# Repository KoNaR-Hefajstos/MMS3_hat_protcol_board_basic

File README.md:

# Zestaw template'ów kompatybilnych z płytką MMS3 i systemem ChainBus

### Łączenie hat'ów
<p> Na jednym MMS3 można zamontować do 8 hatów. Łączy się przez wpinianie kolejnego Hat'a do złącza ChainBus wcześniejszego

### Komunikacja oraz sterowanie
<p> ChainBus jest w pełni cyfrowy. GPIO nie sterują bezpośrednio funkcjonalnością, tylko poprzez magistrale komunikacyjne i IC.
<p> Znaczy to, że zamiast używać GPIO do przełączania LED'a, odczytywania krańcówek czy zadawania PWM'a musisz zaimplementować jakiegoś IC który to robi. Np:
<p> MCU --> expander gpio po I2C --> Dioda LED
<p> MCU wybiera do którego hat'a się podpina przy użyciu bus switcha. To znaczy że magistrale I2C, SPI i UART są niezależne od siebie na każdym hat'ie (nie musisz się martwić o zajęte adresy I2C). Ale musisz pamiętać żeby podpinać sie z busa Chainbus a nie Chainbus_IN (czyli tego za bus swichem)
<p> Dodatkowo w celu identyfikacji każdego hat'a jest na nim pamięć EEPROM po I2C. Możesz użyć np. M24C64-W z obudową SOIC-8 i addresie 1010000 (przy A0 A1 A2 zwartych do GND)

### Zasilanie
<p> Przez złącze ChainBus idzie następujące zasilanie

|          |   Napięcie    | Prąd na wszystkie haty | Prąd dla jednego hat'a |
| -------- | :-----------: | :--------------------: | ---------------------: |
| 5V       |      5V       |           1A           |                  125mA |
| 12V stby |      12V      |          0.5A          |                   65mA |
| BRD_VIN  | Od 12V do 48V |          1.5A          |                  185mA |

<p> Prąd dla jednego hat'a został policzony w wypadku kiedy wszystkie 8 hat'ów jest zamontowanych. Jeśli na jeden MMS zamontujesz mniej hat'ów to każdy może pociągnąć więcej prądu.

<p> Hat'y powinny obsługiwać do 48V z BRD_VIN. Komponenty powinny być dostosowane aż do tego napięcia.

<p> Jeśli twoja płytka potrzebuje więcej mocy niż ile ChainBus daje, to można dodatkowo podłączyć Vin po XT60 która obsługuje około 60A.

<p> Jeśli potrzebujesz innych napięć to możesz użyć gotowej przetwonicy step-down z template'a. Można wybierać z niej 24V, 12V, 9V i 6V2. Wszystkie na 2A.

### Template Mechaniczny
<p> Nie możesz zmieniać wielkości PCB, rozstawienia otworów montażowych oraz pozycji złącz chainbus (02x16 SMD, 2.54 raster) żeby płytka była kompatybilna z ChainBus'em
<p> Jeśli są potrzebne będą w twoim projekcie, to na płytce zostały rozstawione złącza XT60 oraz konwerter step down. Te elementy nie zostały jeszcze przetestowane, ale powinny działać.
<p>Jeśli twój projekt ich nie potrzebuje to możesz je na spokojnie usunąć.

### Wyprowadzenia
<p> Po środku płytki na górze jest złącze Chainbus. Na od front'u  jest żeńskie, na Back'u jest męskie.
<p> Na dolnej krawędzi płytki powinny być umieszczone złącza wyjścia/wejścia. Na lewej złacza XT60 jeśli ich używasz, a na prawej wszystkie elementy konfiguracyjne i debugowe (potencjometry, przyciski, LED'y).

<p> Domyślnie jako złącz używamy JST-XH 2.5mm. Producent mówi że obsługują do 3A

### Przykładowy hat
[Sterownik silników krokowych. Komunikacja po SPI](https://github.com/KoNaR-Hefajstos/MMS3_hat_stepper_controler)

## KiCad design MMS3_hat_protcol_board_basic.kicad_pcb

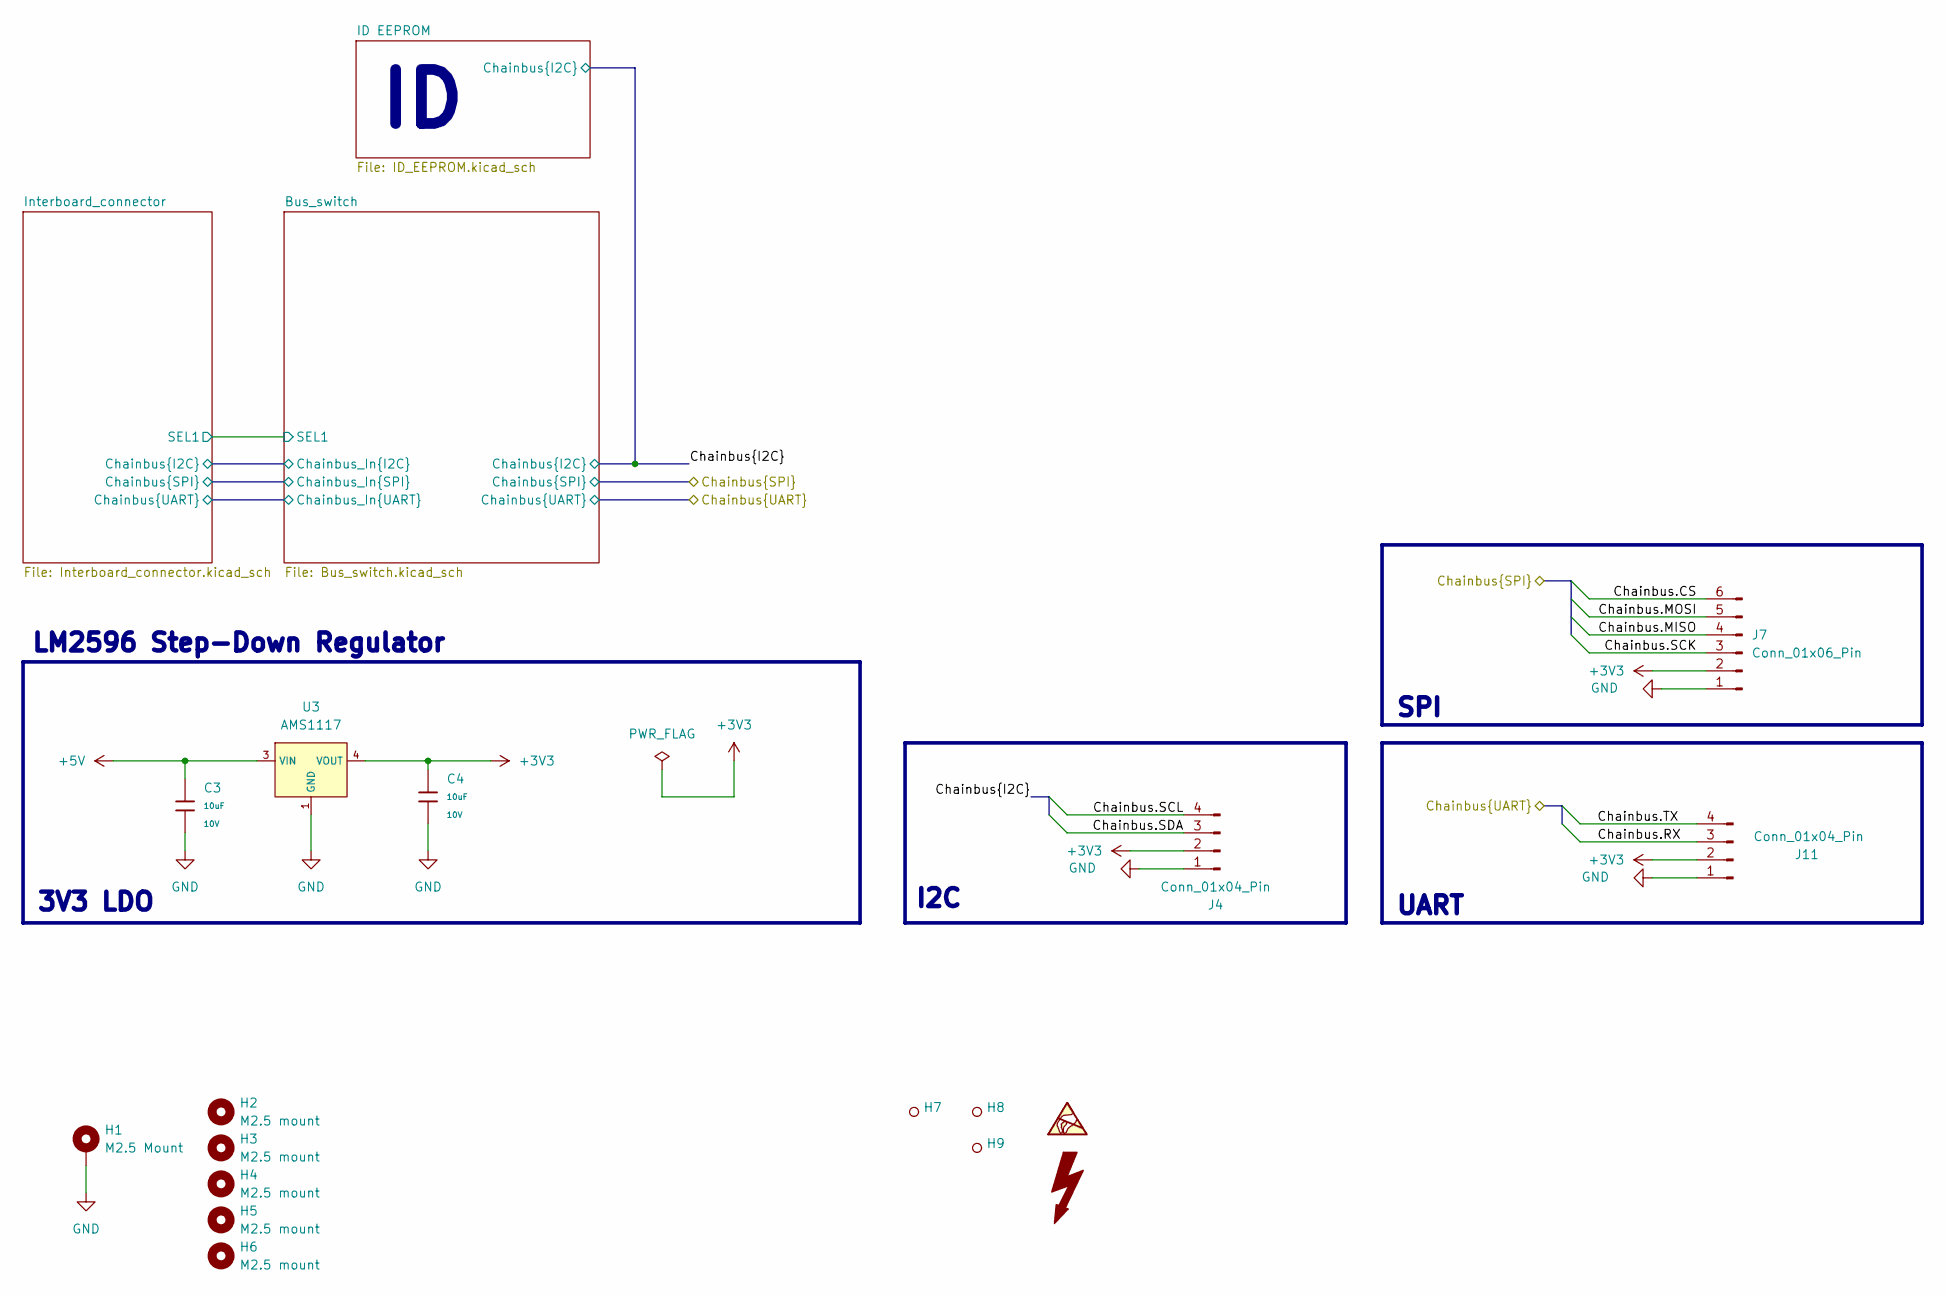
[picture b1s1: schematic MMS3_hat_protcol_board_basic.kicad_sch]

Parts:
C3, C4: 10uF; C_0603; Voltage Rated 10V; Tolerance ±10%; Part CL10A106KP8NNNC; LCSC C19702
H1: M2.5 Mount; MountingHole_2.7mm_M2.5_DIN965_Pad_TopOnly
H2, H3, H4, H5, H6: M2.5 mount; MountingHole_2.7mm_M2.5
H7, H8, H9: Hole_Tooling_JLCPCB
J4, J11: Conn_01x04_Pin; JST_XH_S4B-XH-A_1x04_P2.50mm_Horizontal
J7: Conn_01x06_Pin; JST_XH_S6B-XH-A_1x06_P2.50mm_Horizontal
U3: AMS1117; SOT-223-3_L6.5-W3.4-P2.30-LS7.0-BR; Output Voltage 3.3V; Dropout Voltage 1.3V@(800mA); Part AMS1117-3.3; LCSC C6186

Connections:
+3V3: C4.1, J4.2, J7.2, J11.2, U3.2 (VOUT), U3.4 (VOUT); also elsewhere on the board
+5V: C3.1, U3.3 (VIN); also elsewhere on the board
/Chainbus.CS: J7.6; also elsewhere on the board
/Chainbus.MISO: J7.4; also elsewhere on the board
/Chainbus.MOSI: J7.5; also elsewhere on the board
/Chainbus.RX: J11.3; also elsewhere on the board
/Chainbus.SCK: J7.3; also elsewhere on the board
/Chainbus.SCL: J4.4; also elsewhere on the board
/Chainbus.SDA: J4.3; also elsewhere on the board
/Chainbus.TX: J11.4; also elsewhere on the board
GND: C3.2, C4.2, H1.1 (1_1), J4.1, J7.1, J11.1, U3.1 (GND); also elsewhere on the board

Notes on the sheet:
3V3 LDO
SPI
I2C
LM2596 Step-Down Regulator
UART

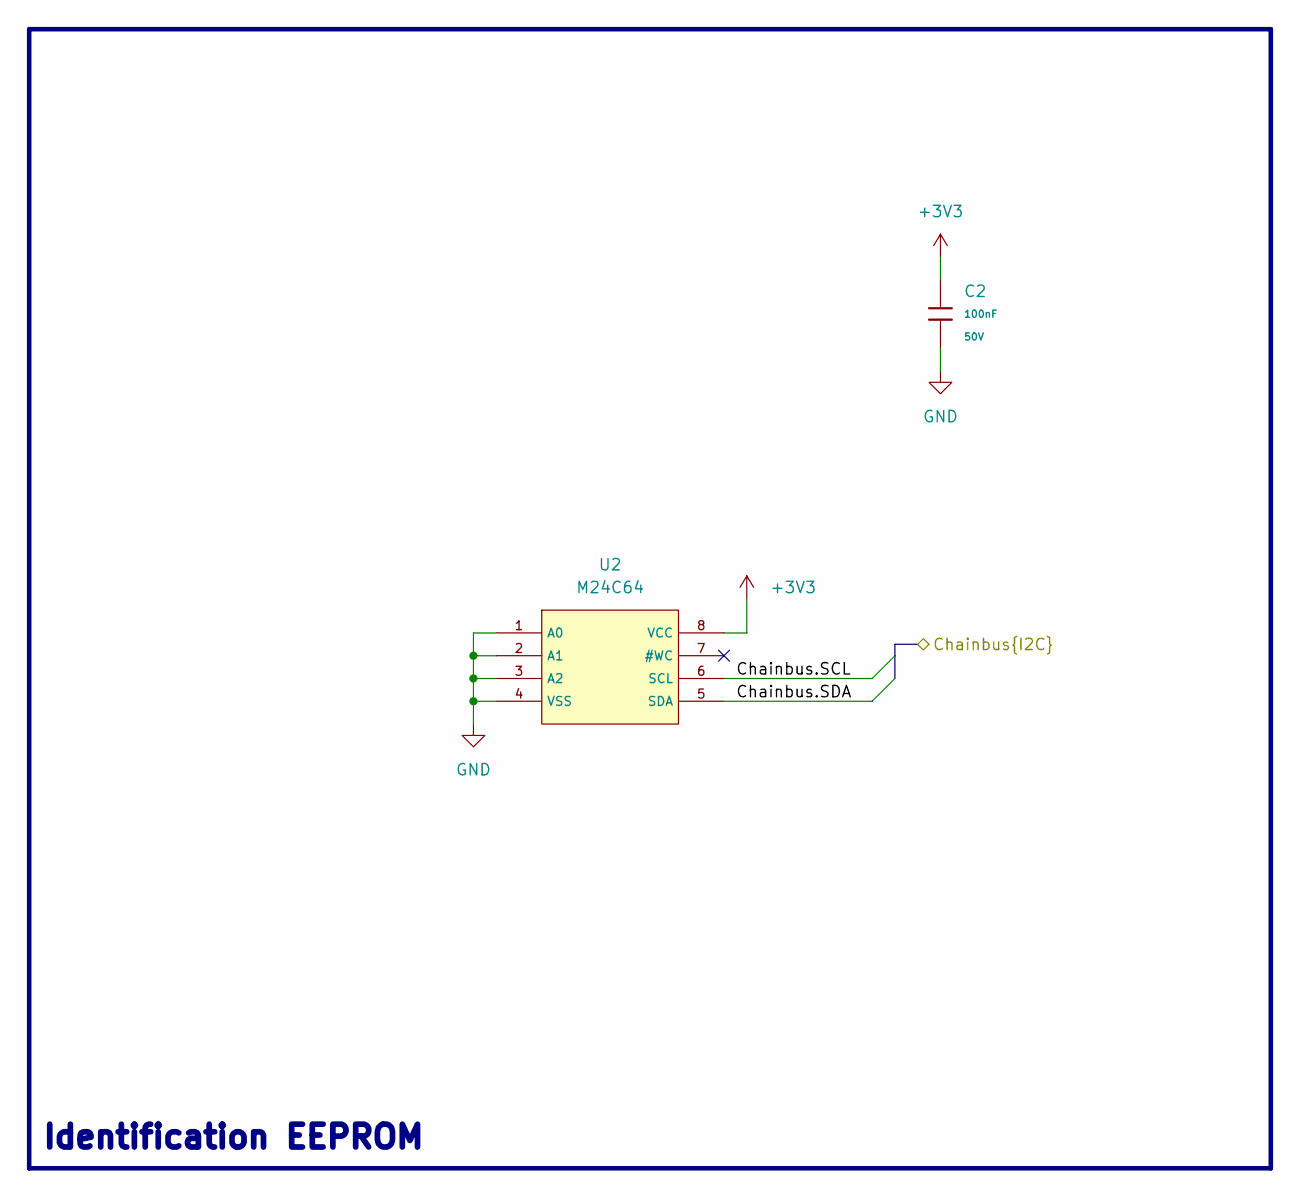
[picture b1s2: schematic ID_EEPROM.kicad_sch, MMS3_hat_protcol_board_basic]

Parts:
C2: 100nF; C_0603; Voltage Rated 50V; Tolerance ±10%; Part CC0603KRX7R9BB104; LCSC C14663
U2: M24C64; SOIC-8_L5.0-W4.0-P1.27-LS6.0-BL; Supply Voltage 1.8V~5.5V; Part M24C64-RMN6TP; LCSC C79988

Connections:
+3V3: C2.1, U2.8 (VCC); also elsewhere on the board
/Chainbus.SCL: U2.6 (SCL); also elsewhere on the board
/Chainbus.SDA: U2.5 (SDA); also elsewhere on the board
GND: C2.2, U2.1 (A0), U2.2 (A1), U2.3 (A2), U2.4 (VSS); also elsewhere on the board

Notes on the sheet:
Identification EEPROM

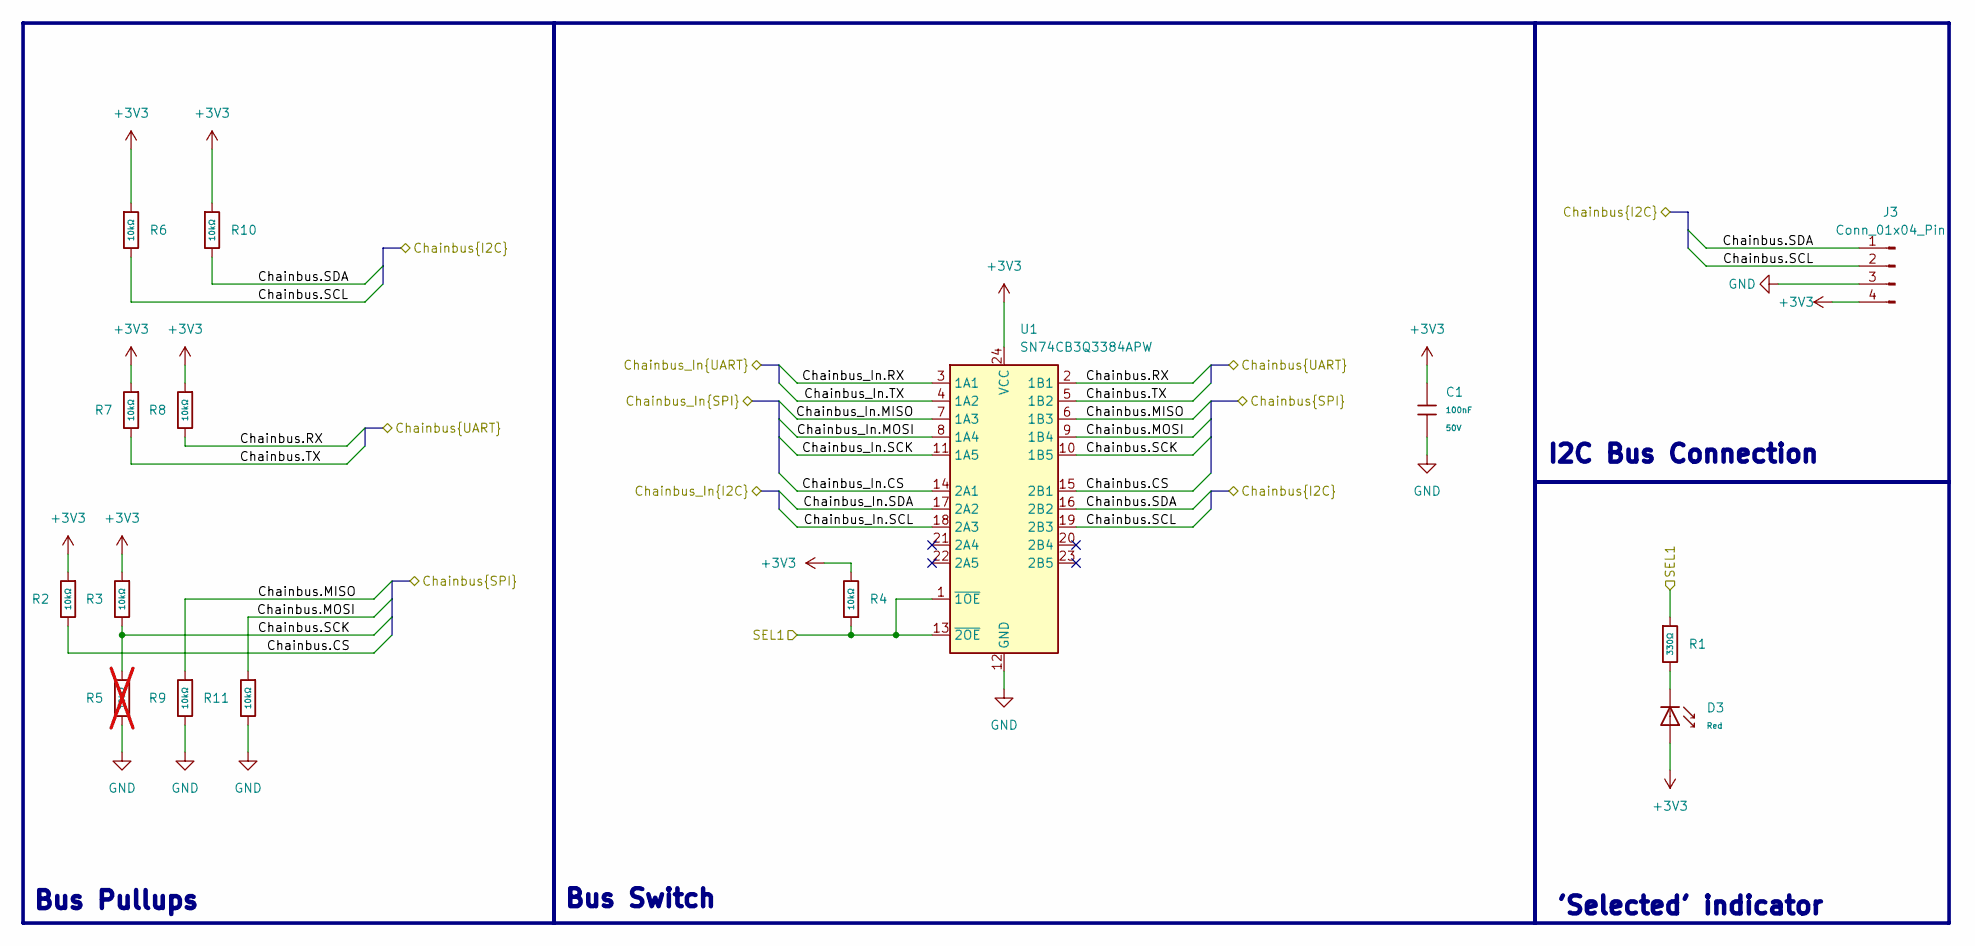
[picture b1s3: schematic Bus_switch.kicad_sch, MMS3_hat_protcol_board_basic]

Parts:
C1: 100nF; C_0603; Voltage Rated 50V; Tolerance ±10%; Part CC0603KRX7R9BB104; LCSC C14663
D3: Red; D_0603; Part KT-0603R; LCSC C2286
J3: Conn_01x04_Pin; PinHeader_1x04_P2.54mm_Vertical
R1: 330Ω; R_0402; Overload Voltage (Max) 50V; Tolerance ±1%; Part 0402WGF3300TCE; LCSC C25104
R2, R3, R4, R6, R7, R8, R9, R10, R11: 10kΩ; R_0402; Overload Voltage (Max) 50V; Tolerance ±1%; Part 0402WGF1002TCE; LCSC C25744
R5: 10kΩ; R_0402; Overload Voltage (Max) 50V; Tolerance ±1%; Part 0402WGF1002TCE; LCSC C25744; not fitted
U1: SN74CB3Q3384APW; TSSOP-24_4.4x7.8mm_P0.65mm; LCSC C469874

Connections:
+3V3: C1.1, D3.2, J3.4, R2.1, R3.1, R4.2, R6.1, R7.1, R8.1, R10.1, U1.24 (VCC); also elsewhere on the board
/Bus_switch/Chainbus_In.CS: U1.14 (2A1); also elsewhere on the board
/Bus_switch/Chainbus_In.MISO: U1.7 (1A3); also elsewhere on the board
/Bus_switch/Chainbus_In.MOSI: U1.8 (1A4); also elsewhere on the board
/Bus_switch/Chainbus_In.RX: U1.3 (1A1); also elsewhere on the board
/Bus_switch/Chainbus_In.SCK: U1.11 (1A5); also elsewhere on the board
/Bus_switch/Chainbus_In.SCL: U1.18 (2A3); also elsewhere on the board
/Bus_switch/Chainbus_In.SDA: U1.17 (2A2); also elsewhere on the board
/Bus_switch/Chainbus_In.TX: U1.4 (1A2); also elsewhere on the board
/Bus_switch/SEL1: R1.1, R4.1, U1.1 (~1OE), U1.13 (~2OE); also elsewhere on the board
/Chainbus.CS: R2.2, U1.15 (2B1); also elsewhere on the board
/Chainbus.MISO: R9.1, U1.6 (1B3); also elsewhere on the board
/Chainbus.MOSI: R11.1, U1.9 (1B4); also elsewhere on the board
/Chainbus.RX: R8.2, U1.2 (1B1); also elsewhere on the board
/Chainbus.SCK: R3.2, R5.1, U1.10 (1B5); also elsewhere on the board
/Chainbus.SCL: J3.2, R6.2, U1.19 (2B3); also elsewhere on the board
/Chainbus.SDA: J3.1, R10.2, U1.16 (2B2); also elsewhere on the board
/Chainbus.TX: R7.2, U1.5 (1B2); also elsewhere on the board
GND: C1.2, J3.3, R5.2, R9.2, R11.2, U1.12 (GND); also elsewhere on the board
unnamed: D3.1, R1.2

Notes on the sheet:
Bus Switch
Bus Pullups
'Selected' indicator
I2C Bus Connection

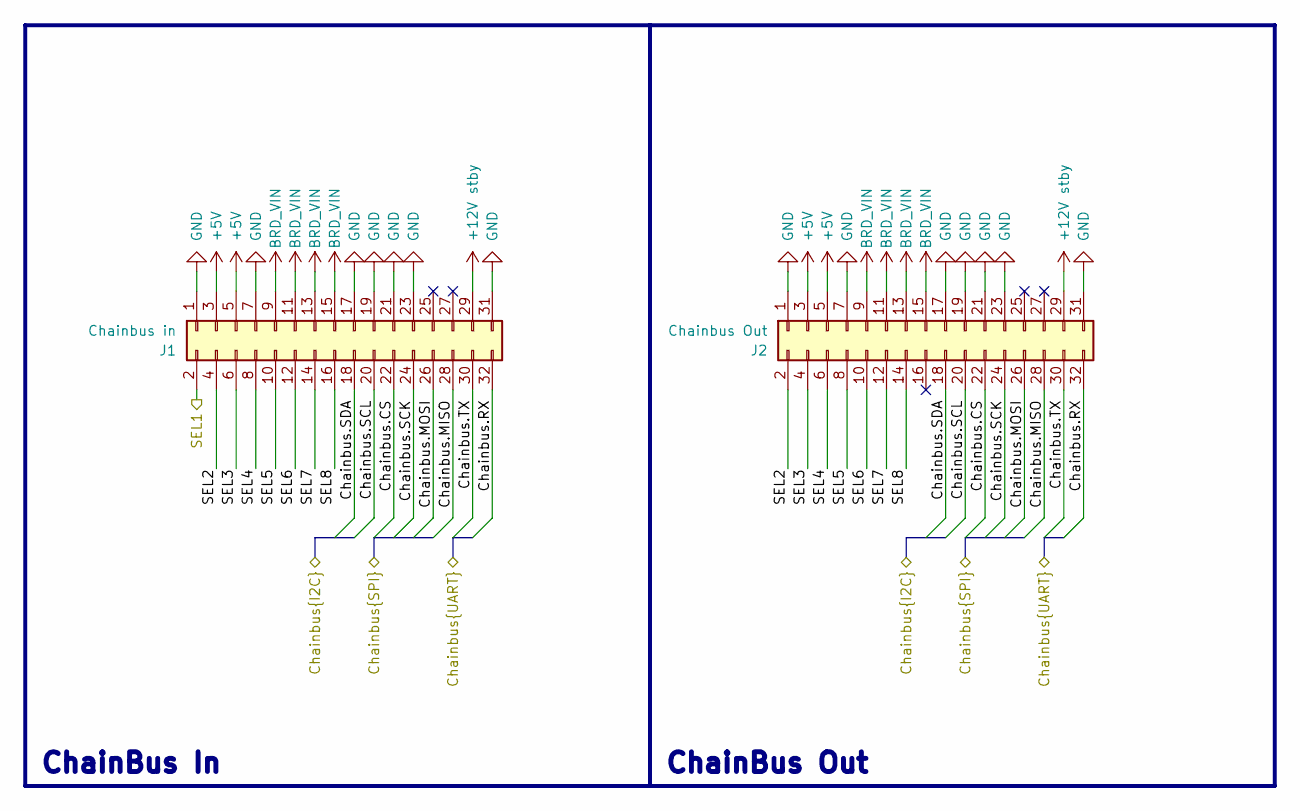
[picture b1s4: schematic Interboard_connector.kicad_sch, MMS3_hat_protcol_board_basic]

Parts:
J1: Chainbus in; PinHeader_2x16_P2.54mm_Vertical_SMD
J2: Chainbus Out; PinSocket_2x16_P2.54mm_Vertical_SMD

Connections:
+5V: J1.3, J1.5, J2.3, J2.5; also elsewhere on the board
+12V stby: J1.29, J2.29
/Bus_switch/Chainbus_In.CS: J1.22, J2.22; also elsewhere on the board
/Bus_switch/Chainbus_In.MISO: J1.28, J2.28; also elsewhere on the board
/Bus_switch/Chainbus_In.MOSI: J1.26, J2.26; also elsewhere on the board
/Bus_switch/Chainbus_In.RX: J1.32, J2.32; also elsewhere on the board
/Bus_switch/Chainbus_In.SCK: J1.24, J2.24; also elsewhere on the board
/Bus_switch/Chainbus_In.SCL: J1.20, J2.20; also elsewhere on the board
/Bus_switch/Chainbus_In.SDA: J1.18, J2.18; also elsewhere on the board
/Bus_switch/Chainbus_In.TX: J1.30, J2.30; also elsewhere on the board
/Bus_switch/SEL1: J1.2; also elsewhere on the board
/Interboard_connector/SEL2: J1.4, J2.2
/Interboard_connector/SEL3: J1.6, J2.4
/Interboard_connector/SEL4: J1.8, J2.6
/Interboard_connector/SEL5: J1.10, J2.8
/Interboard_connector/SEL6: J1.12, J2.10
/Interboard_connector/SEL7: J1.14, J2.12
/Interboard_connector/SEL8: J1.16, J2.14
BRD_VIN: J1.9, J1.11, J1.13, J1.15, J2.9, J2.11, J2.13, J2.15
GND: J1.1, J1.7, J1.17, J1.19, J1.21, J1.23, J1.31, J2.1, J2.7, J2.17, J2.19, J2.21, J2.23, J2.31; also elsewhere on the board

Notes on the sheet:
ChainBus In
ChainBus Out

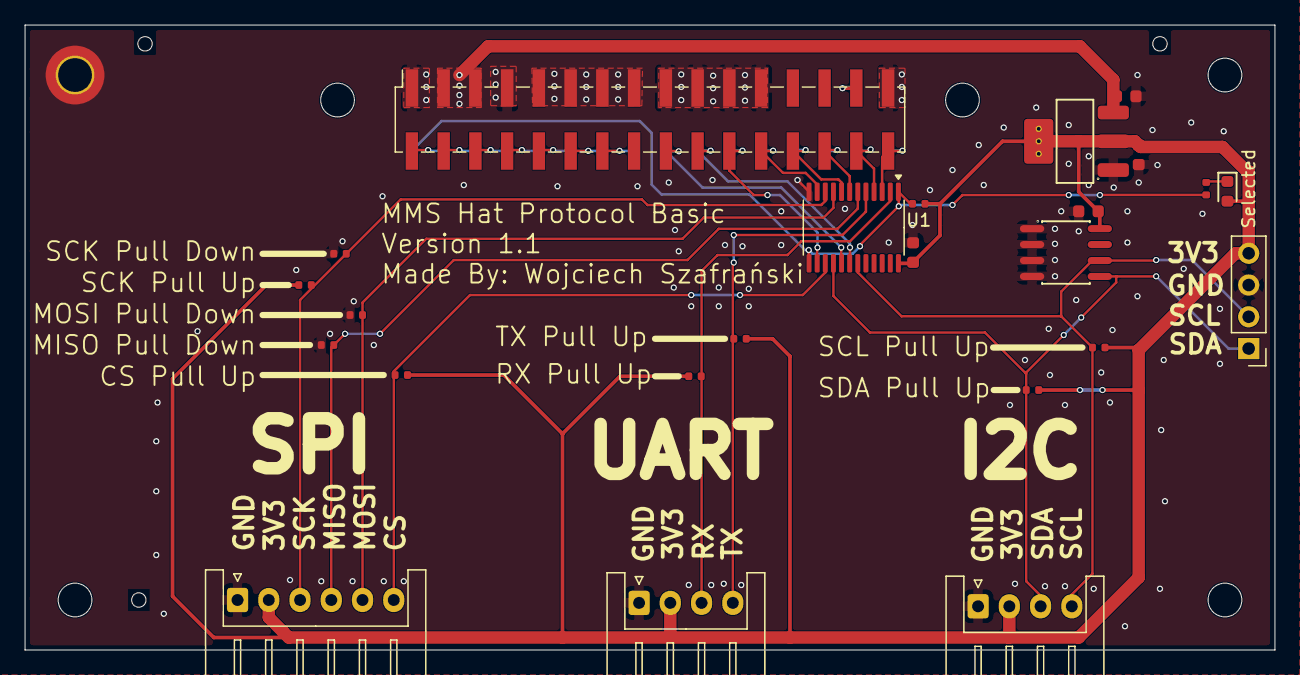
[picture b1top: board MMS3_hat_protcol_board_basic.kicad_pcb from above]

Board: 2 copper layers, 100.0 x 50.0 mm, 34 parts (1 on the bottom side), 30 nets.

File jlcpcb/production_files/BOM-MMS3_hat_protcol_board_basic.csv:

Comment,Designator,Footprint,LCSC,Quantity
100nF,"C1,C2",C_0603,C14663,2
10kΩ,"R10,R11,R2,R3,R4,R6,R7,R8,R9",R_0402,C25744,9
10uF,"C3,C4",C_0603,C19702,2
330Ω,R1,R_0402,C25104,1
AMS1117,U3,SOT-223-3_L6.5-W3.4-P2.30-LS7.0-BR,C6186,1
M24C64,U2,SOIC-8_L5.0-W4.0-P1.27-LS6.0-BL,C79988,1
Red,D3,D_0603,C2286,1
SN74CB3Q3384APW,U1,TSSOP-24_4.4x7.8mm_P0.65mm,C469874,1
Chainbus Out,J2,PinSocket_2x16_P2.54mm_Vertical_SMD,,1
~,H8,Hole_Tooling_JLCPCB,,1
Conn_01x04_Pin,J3,PinHeader_1x04_P2.54mm_Vertical,,1
~,H7,Hole_Tooling_JLCPCB,,1
Conn_01x06_Pin,J7,JST_XH_S6B-XH-A_1x06_P2.50mm_Horizontal,,1
Conn_01x04_Pin,J4,JST_XH_S4B-XH-A_1x04_P2.50mm_Horizontal,,1
Conn_01x04_Pin,J11,JST_XH_S4B-XH-A_1x04_P2.50mm_Horizontal,,1
~,H9,Hole_Tooling_JLCPCB,,1
Chainbus in,J1,PinHeader_2x16_P2.54mm_Vertical_SMD,,1

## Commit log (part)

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2026-03-12 Done. Don't ask questions
